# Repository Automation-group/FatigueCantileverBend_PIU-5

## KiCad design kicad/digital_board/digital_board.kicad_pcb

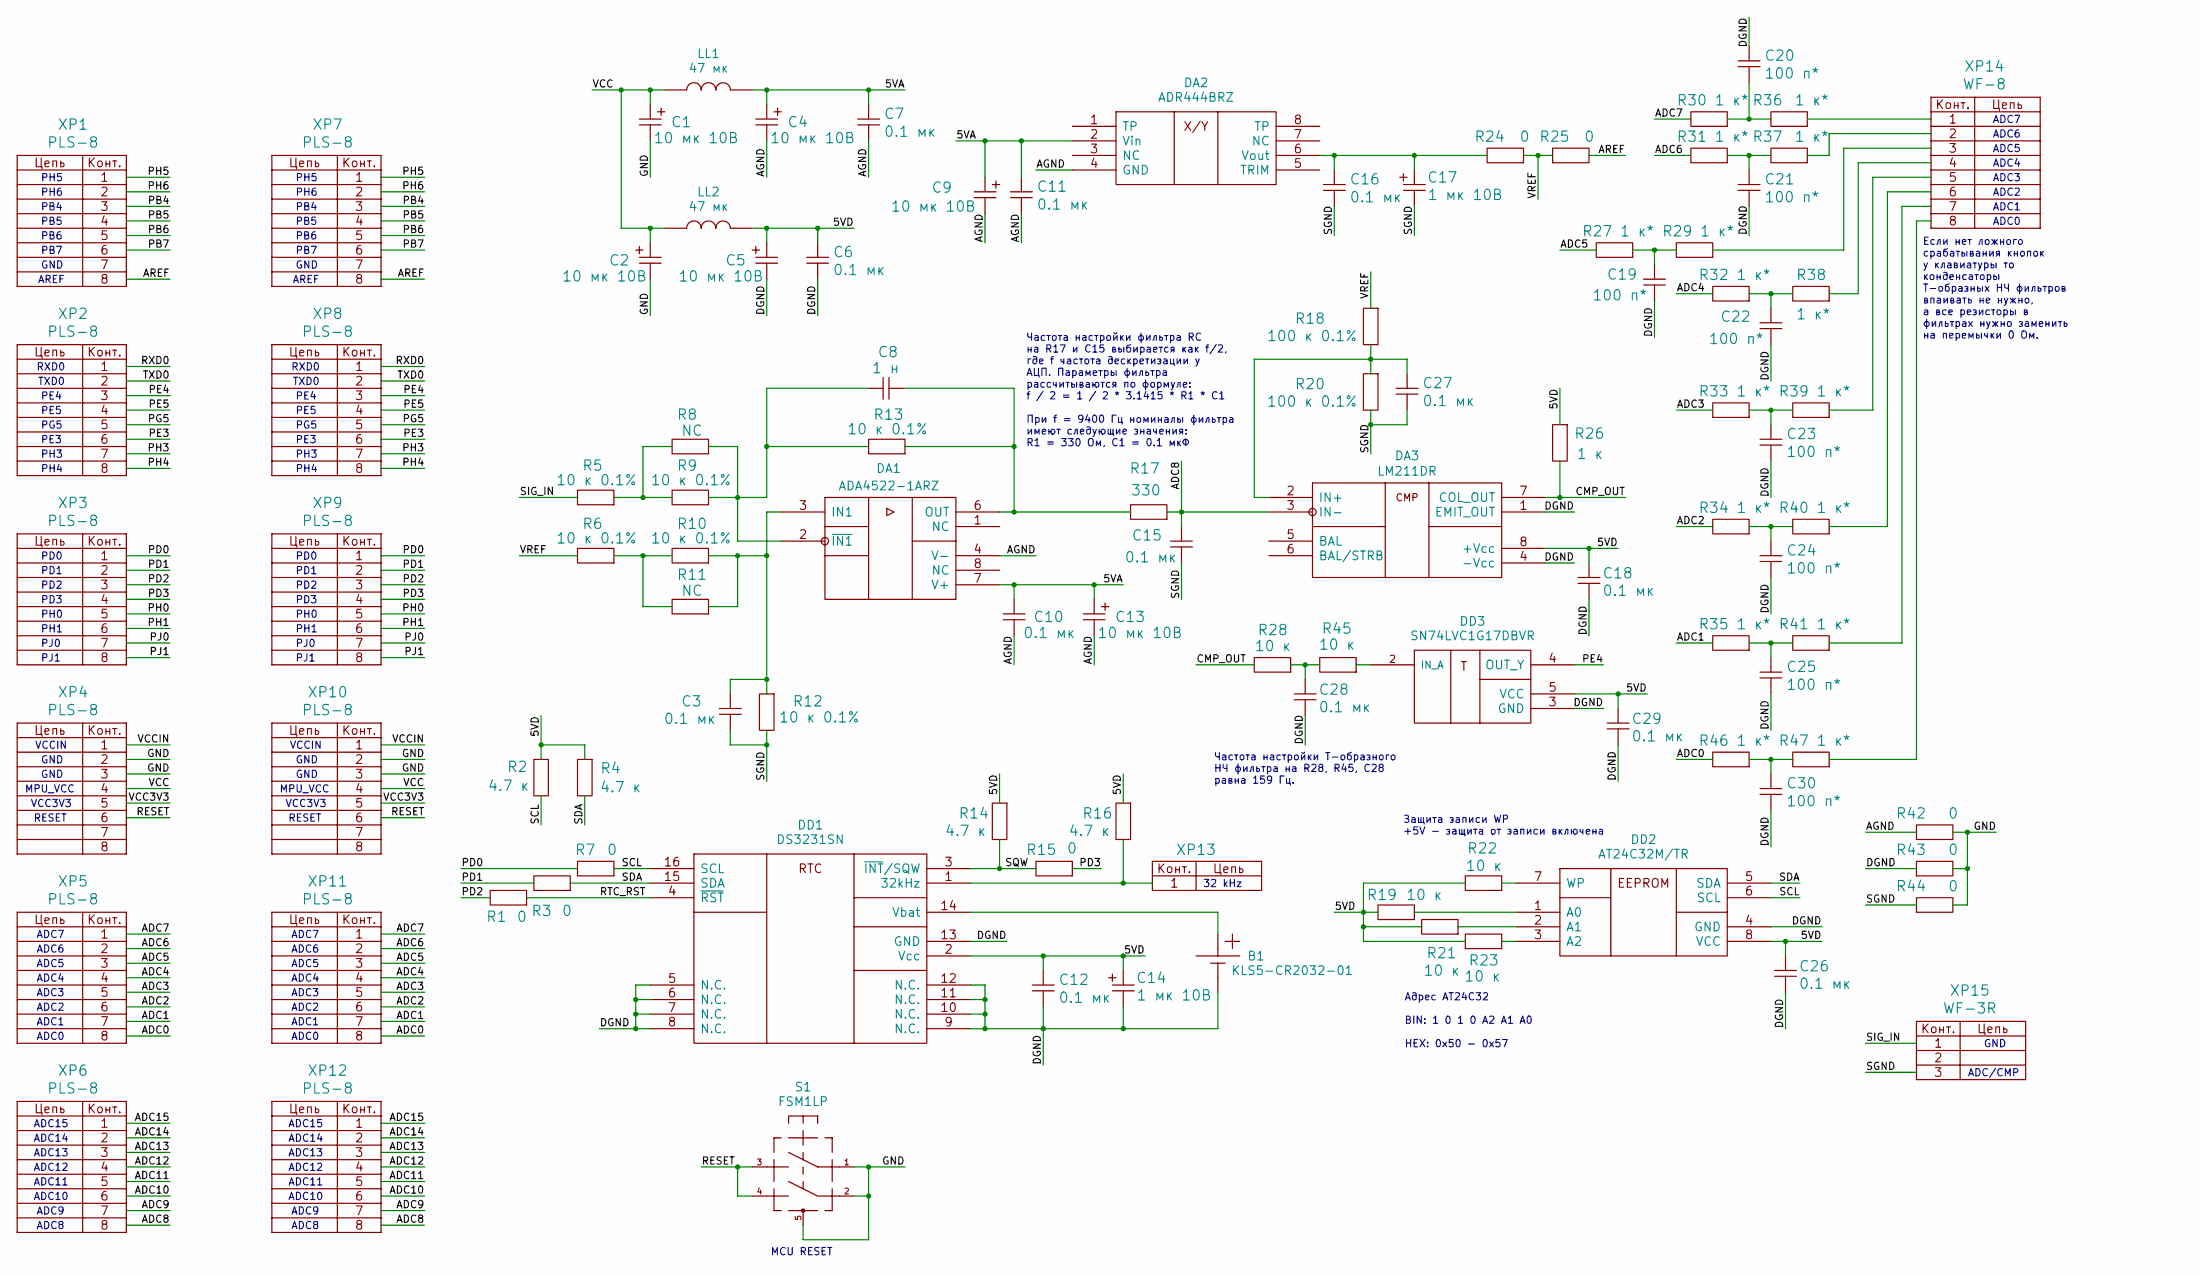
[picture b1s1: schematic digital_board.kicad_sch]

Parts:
B1: KLS5-CR2032-01
C1, C2, C4, C5, C9, C13: 10 мк 10В; CASE_A
C3, C6, C7, C10, C11, C12, C15, C16, C18, C26, C27, C28, C29: 0.1 мк; SMD0805
C8: 1 н; SMD0805
C14, C17: 1 мк 10В; CASE_A
C19, C20, C21, C22, C23, C24, C25, C30: 100 п*; SMD0805
DA1: ADA4522-1ARZ; SOIC8
DA2: ADR444BRZ; SOIC8
DA3: LM211DR; SOIC8
DD1: DS3231SN; SOIC16_RW16
DD2: AT24C32M/TR; SOIC8
DD3: SN74LVC1G17DBVR; SOT753
LL1, LL2: 47 мк; SMD0805
R1, R3, R7, R15, R24, R25, R42, R43, R44: 0; SMD0805
R2, R4, R14, R16: 4.7 к; SMD0805
R5, R6, R9, R10, R12, R13: 10 к 0.1%; SMD0805
R8, R11: NC; SMD0805
R17: 330; SMD0805
R18, R20: 100 к 0.1%; SMD0805
R19, R21, R22, R23, R28, R45: 10 к; SMD0805
R26: 1 к; SMD0805
R27, R29, R30, R31, R32, R33, R34, R35, R36, R37, R38, R39, R40, R41, R46, R47: 1 к*; SMD0805
S1: FSM1LP; SWD_BUTTON
XP1, XP2, XP3, XP4, XP5, XP6, XP7, XP8, XP9, XP10, XP11, XP12: PLS-8; PIN_ARRAY_8x1
XP13: 1_pin_1_0mm
XP14: WF-8
XP15: WF-3R

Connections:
/5VA: C4.1, C7.1, C9.1, C10.1, C11.1, C13.1, DA1.7 (V+), DA2.2 (Vin), LL1.1
/5VD: C5.1, C6.1, C12.1, C14.1, C18.1, C26.1, C29.1, DA3.8 (+Vcc), DD1.2 (Vcc), DD2.8 (VCC), DD3.5 (VCC), LL2.2, R2.1, R4.1, R14.1, R16.1, R19.2, R21.2, R22.2, R23.2, R26.1
/ADC0: R46.2, XP5.8, XP11.8
/ADC1: R35.2, XP5.7, XP11.7
/ADC2: R34.2, XP5.6, XP11.6
/ADC3: R33.2, XP5.5, XP11.5
/ADC4: R32.2, XP5.4, XP11.4
/ADC5: R27.2, XP5.3, XP11.3
/ADC6: R31.2, XP5.2, XP11.2
/ADC7: R30.2, XP5.1, XP11.1
/ADC8: C15.1, DA3.3 (IN-), R17.1, XP6.8, XP12.8
/ADC9: XP6.7, XP12.7
/ADC10: XP6.6, XP12.6
/ADC11: XP6.5, XP12.5
/ADC12: XP6.4, XP12.4
/ADC13: XP6.3, XP12.3
/ADC14: XP6.2, XP12.2
/ADC15: XP6.1, XP12.1
/AGND: C4.2, C7.2, C9.2, C10.2, C11.2, C13.2, DA1.4 (V-), DA2.4 (GND), R42.1
/AREF: R25.2, XP1.8, XP7.8
/CMP_OUT: DA3.7 (COL_OUT), R26.2, R28.2
/DGND: B1.2, C5.2, C6.2, C12.2, C14.2, C18.2, C19.2, C20.1, C21.2, C22.2, C23.2, C24.2, C25.2, C26.2, C28.2, C29.2, C30.2, DA3.1 (EMIT_OUT), DA3.4 (-Vcc), DD1.5 (N.C.), DD1.6 (N.C.), DD1.7 (N.C.), DD1.8 (N.C.), DD1.9 (N.C.), DD1.10 (N.C.), DD1.11 (N.C.), DD1.12 (N.C.), DD1.13 (GND), DD2.4 (GND), DD3.3 (GND), R43.1
/GND: C1.2, C2.2, R42.2, R43.2, R44.2, S1.1, S1.2, S1.5, XP4.2, XP4.3, XP10.2, XP10.3
/PB4: XP1.3, XP7.3
/PB5: XP1.4, XP7.4
/PB6: XP1.5, XP7.5
/PB7: XP1.6, XP7.6
/PD0: R7.2, XP3.1, XP9.1
/PD1: R3.2, XP3.2, XP9.2
/PD2: R1.2, XP3.3, XP9.3
/PD3: R15.1, XP3.4, XP9.4
/PE3: XP2.6, XP8.6
/PE4: DD3.4 (OUT_Y), XP2.3, XP8.3
/PE5: XP2.4, XP8.4
/PG5: XP2.5, XP8.5
/PH0: XP3.5, XP9.5
/PH1: XP3.6, XP9.6
/PH3: XP2.7, XP8.7
/PH4: XP2.8, XP8.8
/PH5: XP1.1, XP7.1
/PH6: XP1.2, XP7.2
/PJ0: XP3.7, XP9.7
/PJ1: XP3.8, XP9.8
/RESET: S1.3, S1.4, XP4.6, XP10.6
/RTC_RST: DD1.4 (~RST), R1.1
/RXD0: XP2.1, XP8.1
/SCL: DD1.16 (SCL), DD2.6 (SCL), R2.2, R7.1
/SDA: DD1.15 (SDA), DD2.5 (SDA), R3.1, R4.2
/SGND: C3.2, C15.2, C16.2, C17.2, C27.2, R12.2, R20.2, R44.1, XP15.3
/SIG_IN: R5.2, XP15.1
/SQW: DD1.3 (~INT/SQW), R14.2, R15.2
/TXD0: XP2.2, XP8.2
/VCC: C1.1, C2.1, LL1.2, LL2.1, XP4.4, XP10.4
/VCC3V3: XP4.5, XP10.5
/VCCIN: XP4.1, XP10.1
/VREF: R6.2, R18.1, R24.1, R25.1
unnamed: C19.1, R27.1, R29.2
unnamed: C20.2, R30.1, R36.2
unnamed: C21.1, R31.1, R37.2
unnamed: C22.1, R32.1, R38.2
unnamed: C23.1, R33.1, R39.2
unnamed: C24.1, R34.1, R40.2
unnamed: C25.1, R35.1, R41.2
unnamed: C28.1, R28.1, R45.2
unnamed: C30.1, R46.1, R47.2
unnamed: C3.1, DA1.3 (IN1), R10.1, R11.1, R12.1
unnamed: C8.2, DA1.6 (OUT), R13.1, R17.2
unnamed: C8.1, DA1.2 (~IN1), R8.1, R9.1, R13.2
unnamed: C16.1, C17.1, DA2.6 (Vout), R24.2
unnamed: C27.1, DA3.2 (IN+), R18.2, R20.1
unnamed: DD1.1 (32kHz), R16.2, XP13.1
unnamed: B1.1, DD1.14 (Vbat)
unnamed: DD2.1 (A0), R19.1
unnamed: DD2.2 (A1), R21.1
unnamed: DD2.3 (A2), R23.1
unnamed: DD2.7 (WP), R22.1
unnamed: DD3.2 (IN_A), R45.1
unnamed: R5.1, R8.2, R9.2
unnamed: R6.1, R10.2, R11.2
unnamed: R29.1, XP14.3
unnamed: R36.1, XP14.1
unnamed: R37.1, XP14.2
unnamed: R38.1, XP14.4
unnamed: R39.1, XP14.5
unnamed: R40.1, XP14.6
unnamed: R41.1, XP14.7
unnamed: R47.1, XP14.8

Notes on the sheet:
ADC4
ADC3
RXD0
ADC11
Если нет ложного срабатывания кнопок у клавиатуры то конденсаторы Т-образных НЧ фильтров впаивать не нужно, а все резисторы в фильтрах нужно заменить на перемычки 0 Ом.
VCCIN
TXD0
ADC5
PE3
MPU_VCC
ADC7
ADC14
PB7
PH0
GND
ADC8
ADC/CMP
PD1
PE4
PG5
ADC0
ADC6
ADC9
PD3
PB5
ADC15
ADC13
ADC10
PH5
PB6
PH4
PH6
PD2
PB4
PH3
ADC12
Адрес AT24C32 BIN: 1 0 1 0 A2 A1 A0 HEX: 0x50 - 0x57
PJ1
Частота настройки Т-образного НЧ фильтра на R28, R45, С28 равна 159 Гц.
32 kHz

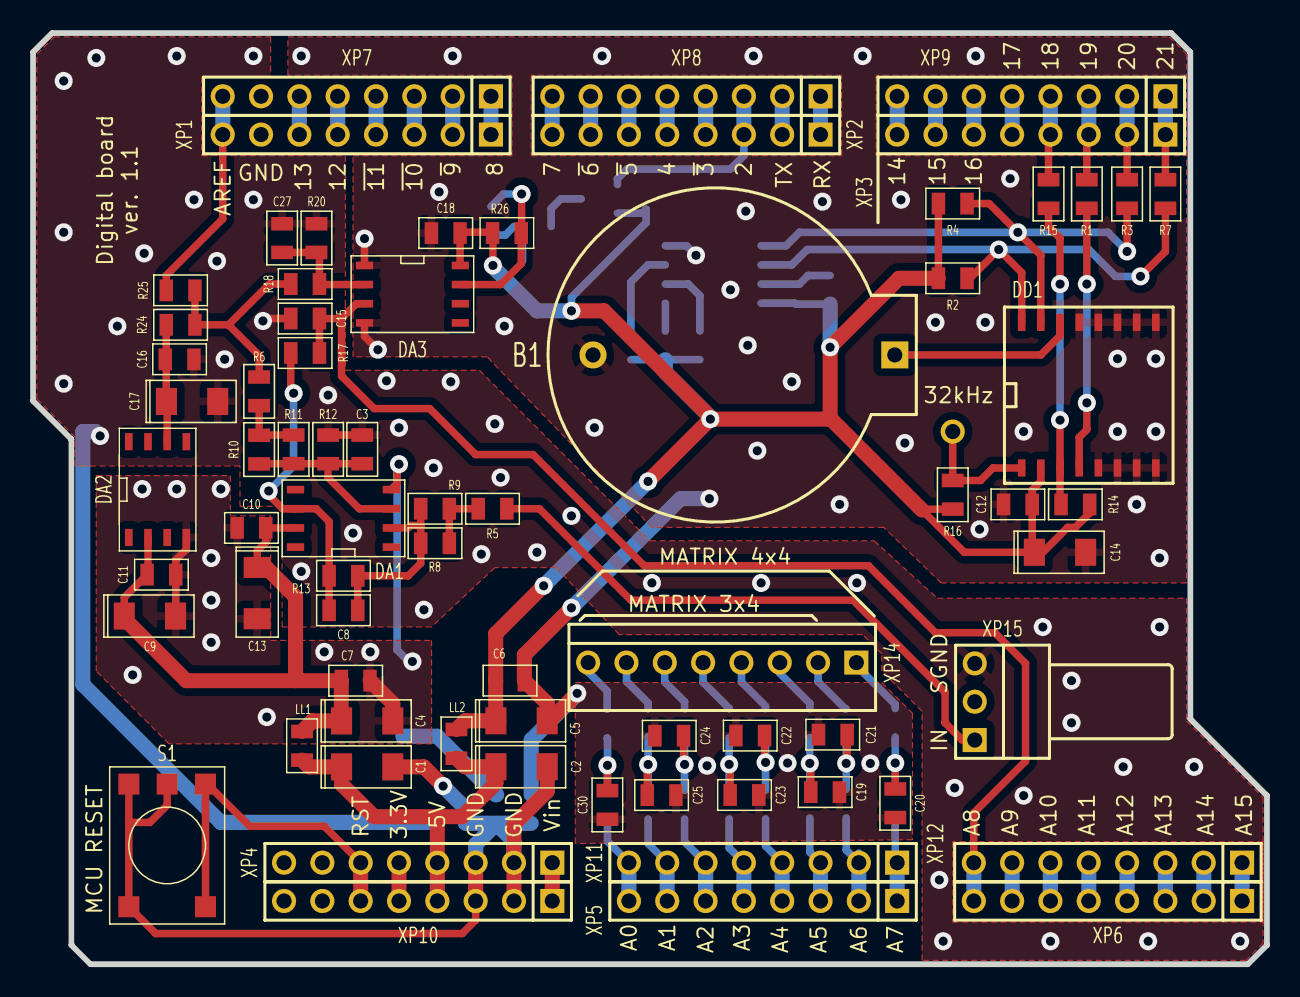
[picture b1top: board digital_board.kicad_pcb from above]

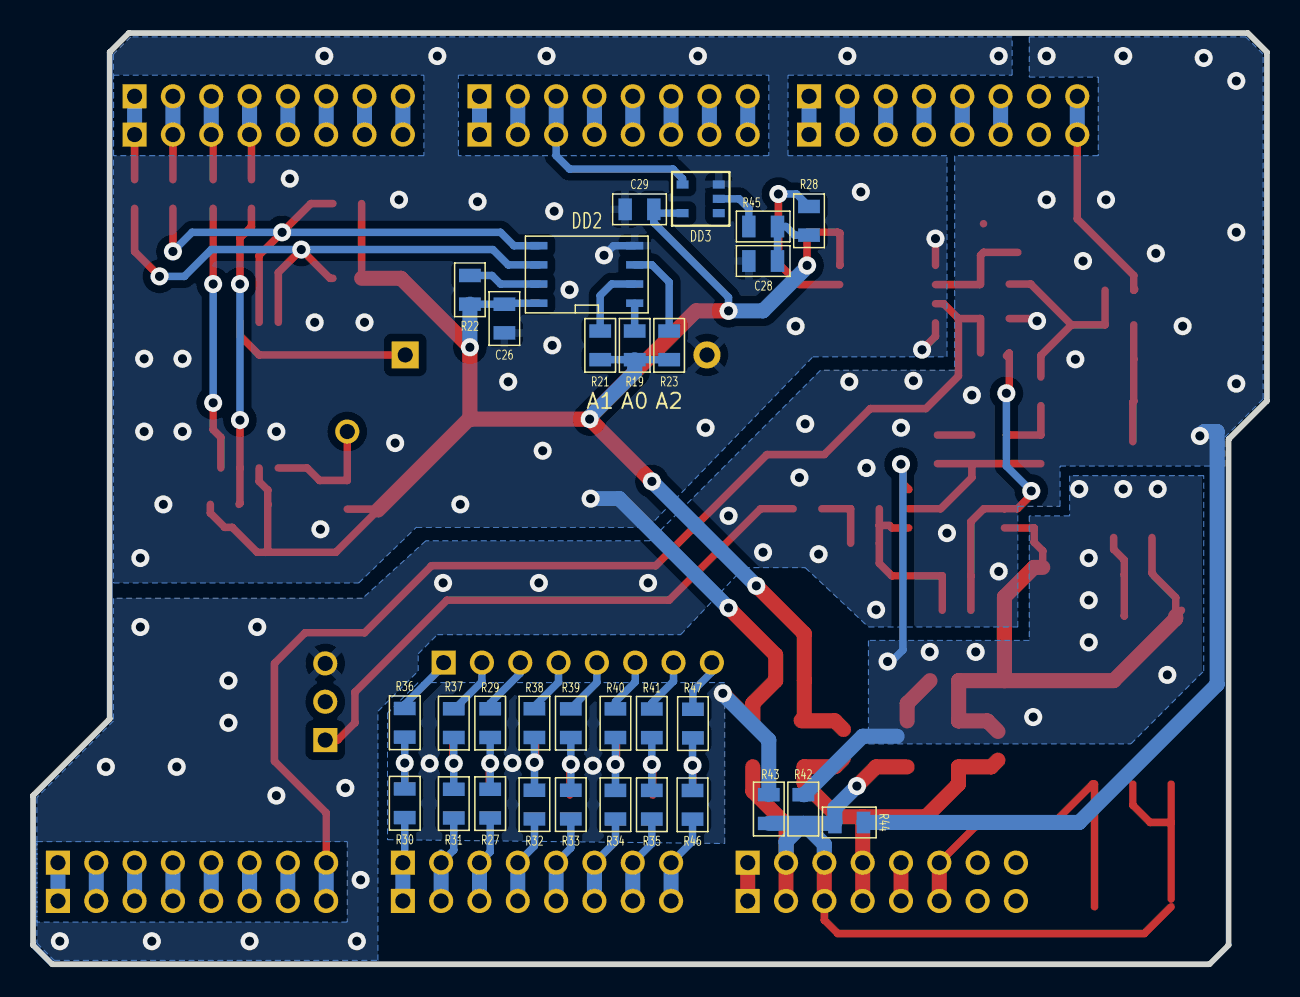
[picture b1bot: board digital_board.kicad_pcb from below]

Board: 2 copper layers, 81.8 x 61.7 mm, 102 parts (30 on the bottom side), 87 nets.

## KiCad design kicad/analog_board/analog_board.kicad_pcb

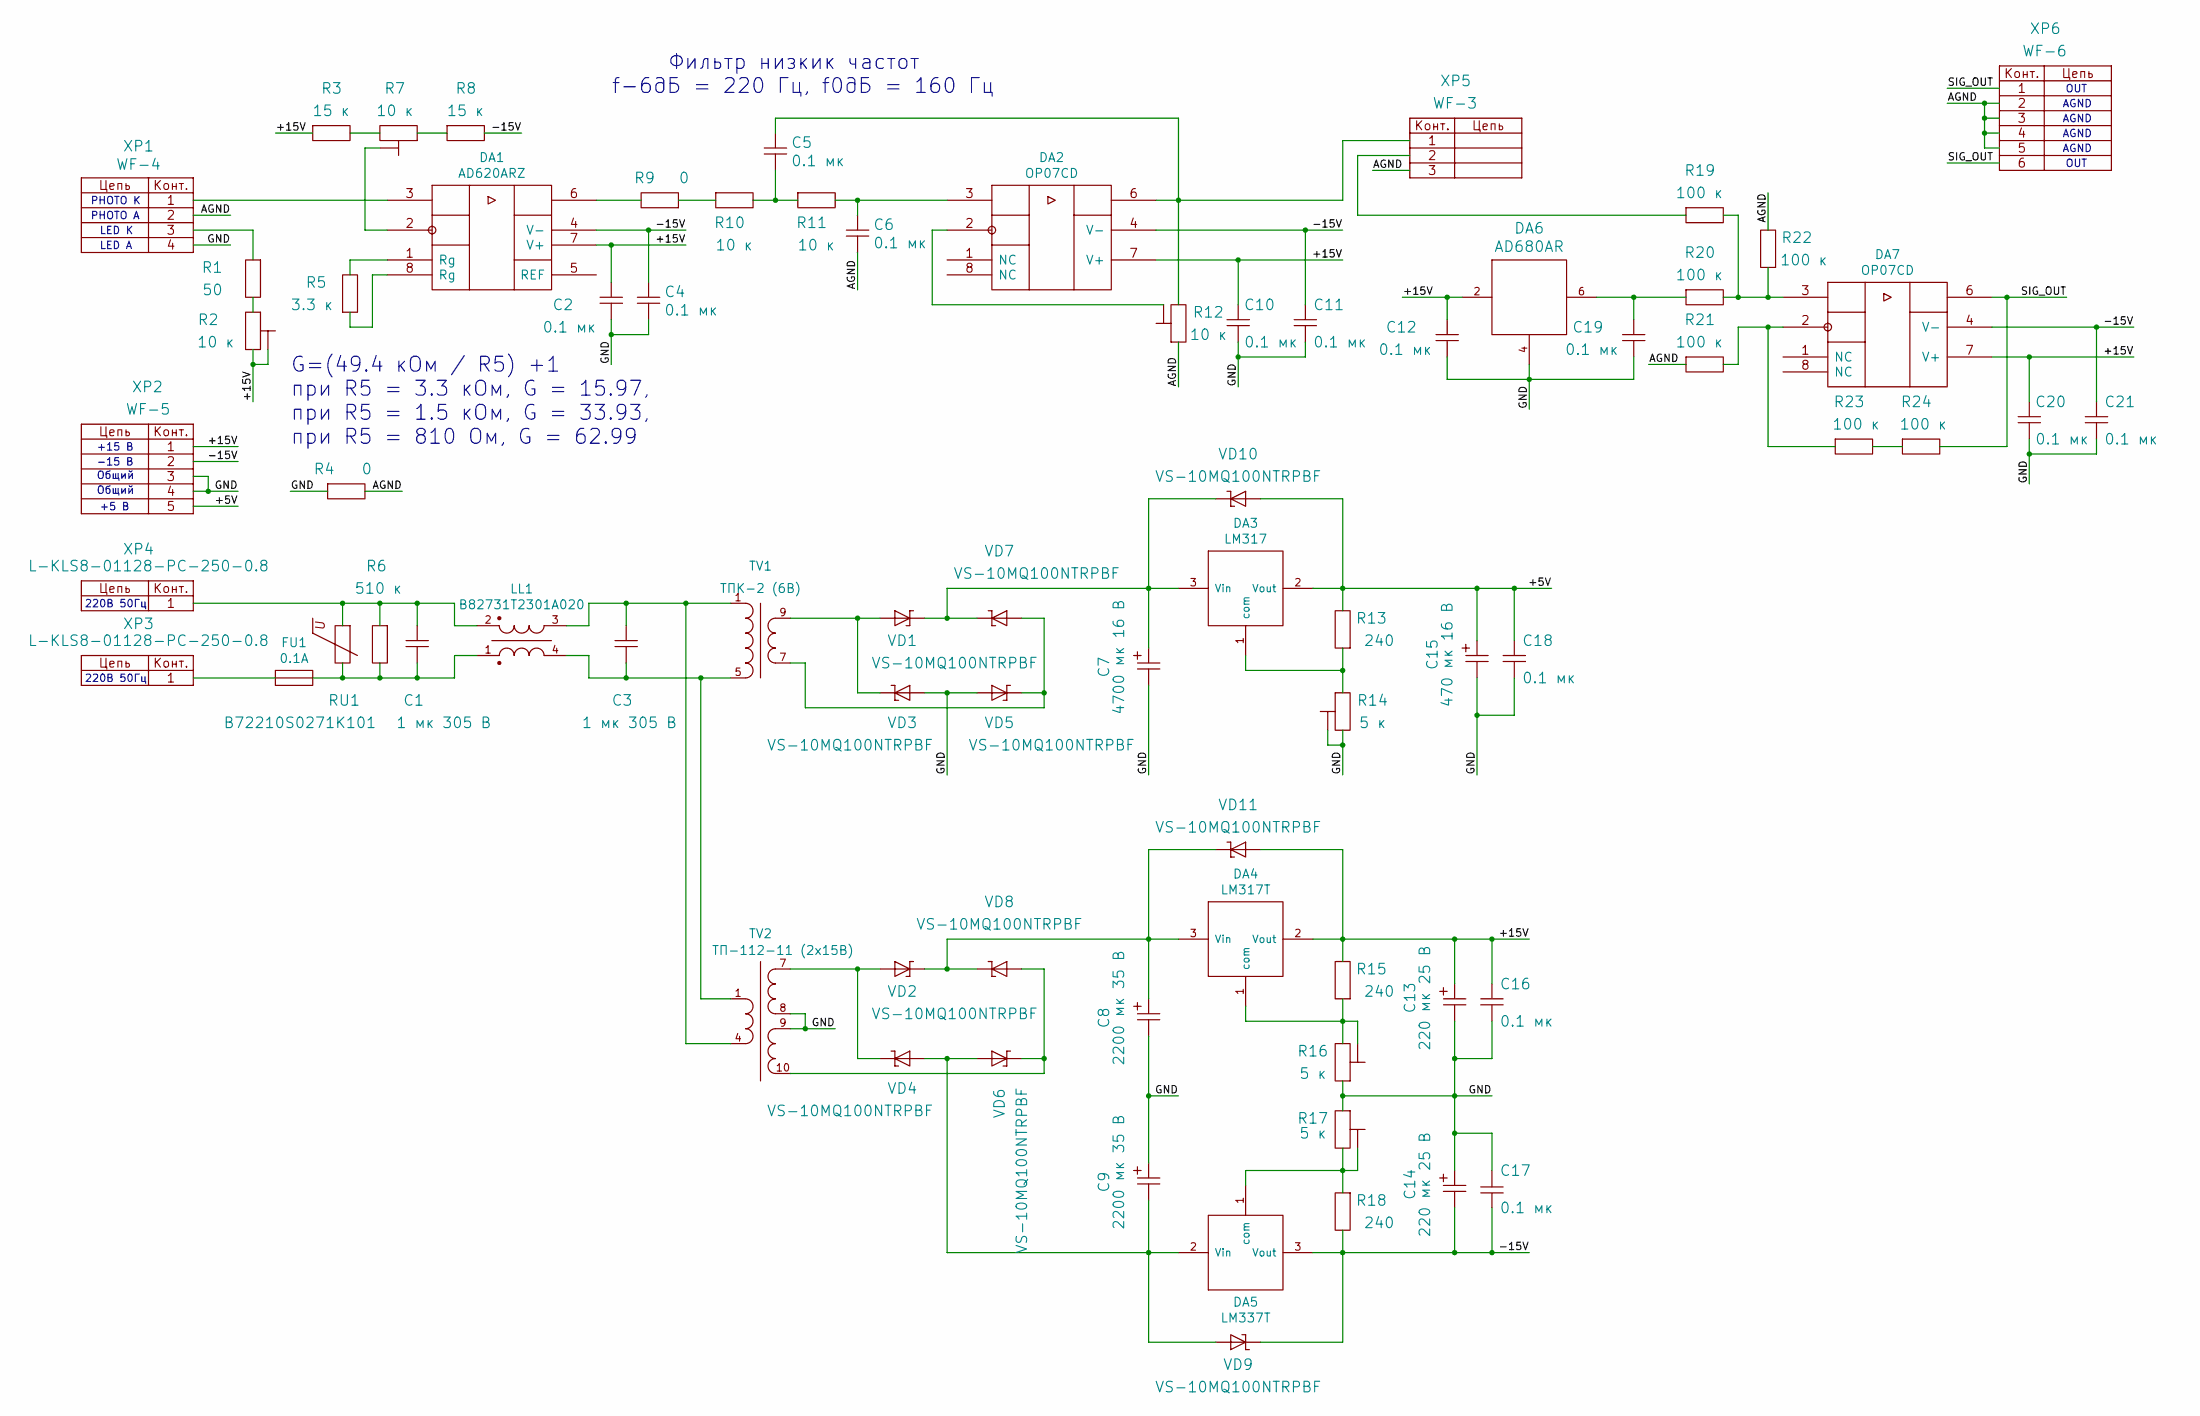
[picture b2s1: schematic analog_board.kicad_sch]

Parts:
C1, C3: 1 мк 305 В; CAPACITOR_B32923_26.5x11
C2, C4, C5, C6, C10, C11, C12, C16, C17, C18, C19, C20, C21: 0.1 мк; SMD0805
C7: 4700 мк 16 В; CAPACITOR_7.62_D16
C8, C9: 2200 мк 35 В; CAPACITOR_7.62_D16
C13, C14: 220 мк 25 В; CAPACITOR_3_D8
C15: 470 мк 16 В; CAPACITOR_3_D8
DA1: AD620ARZ; SOIC8
DA2, DA7: OP07CD; SOIC8
DA3: LM317; TO220_RAD_16.5x15
DA4: LM317T; TO220_RAD_16.5x15
DA5: LM337T; TO220_RAD_16.5x15
DA6: AD680AR; SOIC8
FU1: 0.1A; FU_PTF15B
LL1: B82731T2301A020; EMI_EPCOS_B82731T
R1: 50; SMD0805
R2, R7, R12: 10 к; Electron_3296W
R3, R8: 15 к; SMD0805
R4, R9: 0; SMD0805
R5: 3.3 к; SMD0805
R6: 510 к; SMD2512
R10, R11: 10 к; SMD0805
R13, R15, R18: 240; SMD0805
R14, R16, R17: 5 к; Electron_3296W
R19, R20, R21, R22, R23, R24: 100 к; SMD0805
RU1: B72210S0271K101; RU_EPCOS_B72210S0271K101_12х5
TV1: ТПК-2 (6В); TPG2-12
TV2: ТП-112-11 (2х15В); TP112-11
VD1, VD2, VD3, VD4, VD5, VD6, VD7, VD8, VD9, VD10, VD11: VS-10MQ100NTRPBF; SMA
XP1: WF-4
XP2: WF-5
XP3, XP4: L-KLS8-01128-PC-250-0.8; TERMINAL_KLS8-01128_6.3mm
XP5: WF-3
XP6: WF-6

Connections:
/+5V: C15.1, C18.1, DA3.2 (Vout), R13.2, VD10.1, XP2.5
/+15V: C2.1, C10.1, C12.1, C13.1, C16.1, C20.1, DA1.7 (V+), DA2.7 (V+), DA4.2 (Vout), DA6.2 (Vin), DA7.7 (V+), R2.2, R2.3, R3.1, R15.2, VD11.1, XP2.1
/-15V: C4.1, C11.1, C14.2, C17.1, C21.1, DA1.4 (V-), DA2.4 (V-), DA5.3 (Vout), DA7.4 (V-), R8.2, R18.2, VD9.2, XP2.2
/AGND: C6.2, R4.2, R12.1, R21.1, R22.2, XP1.2, XP5.3, XP6.2, XP6.3, XP6.4, XP6.5
/GND: C2.2, C4.2, C7.2, C8.2, C9.1, C10.2, C11.2, C12.2, C13.2, C14.1, C15.2, C16.2, C17.2, C18.2, C19.2, C20.2, C21.2, DA6.4 (Gnd), R4.1, R14.2, R14.3, R16.1, R17.1, TV2.8, TV2.9, VD3.1, VD5.1, XP1.4, XP2.3, XP2.4
/SIG_OUT: DA7.6, R24.2, XP6.1, XP6.6
unnamed: C1.1, LL1.2, R6.1, RU1.1, XP4.1
unnamed: C1.2, FU1.2, LL1.1, R6.2, RU1.2
unnamed: C3.1, LL1.3, TV1.1, TV2.4
unnamed: C3.2, LL1.4, TV1.5, TV2.1
unnamed: C5.1, DA2.6, R12.3, XP5.1
unnamed: C5.2, R10.2, R11.1
unnamed: C6.1, DA2.3, R11.2
unnamed: C7.1, DA3.3 (Vin), VD1.2, VD7.2, VD10.2
unnamed: C8.1, DA4.3 (Vin), VD2.2, VD8.2, VD11.2
unnamed: C9.2, DA5.2 (Vin), VD4.1, VD6.1, VD9.1
unnamed: C19.1, DA6.6 (Vout), R20.1
unnamed: DA1.1 (Rg), R5.2
unnamed: DA1.2, R7.2
unnamed: DA1.3, XP1.1
unnamed: DA1.6, R9.2
unnamed: DA1.8 (Rg), R5.1
unnamed: DA2.2, R12.2
unnamed: DA3.1 (com), R13.1, R14.1
unnamed: DA4.1 (com), R15.1, R16.2, R16.3
unnamed: DA5.1 (com), R17.2, R17.3, R18.1
unnamed: DA7.2, R21.2, R23.1
unnamed: DA7.3, R19.2, R20.2, R22.1
unnamed: FU1.1, XP3.1
unnamed: R1.1, XP1.3
unnamed: R1.2, R2.1
unnamed: R3.2, R7.3
unnamed: R7.1, R8.1
unnamed: R9.1, R10.1
unnamed: R19.1, XP5.2
unnamed: R23.2, R24.1
unnamed: TV1.7, VD5.2, VD7.1
unnamed: TV1.9, VD1.1, VD3.2
unnamed: TV2.7, VD2.1, VD4.2
unnamed: TV2.10, VD6.2, VD8.1

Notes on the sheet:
-15 В
Фильтр низкик частот f-6дБ = 220 Гц, f0дБ = 160 Гц
Общий
PHOTO A
AGND
LED A
OUT
G=(49.4 кОм / R5) +1 при R5 = 3.3 кОм, G = 15.97, при R5 = 1.5 кОм, G = 33.93, при R5 = 810 Ом, G = 62.99
LED K
220В 50Гц
+5 В
+15 В
PHOTO K

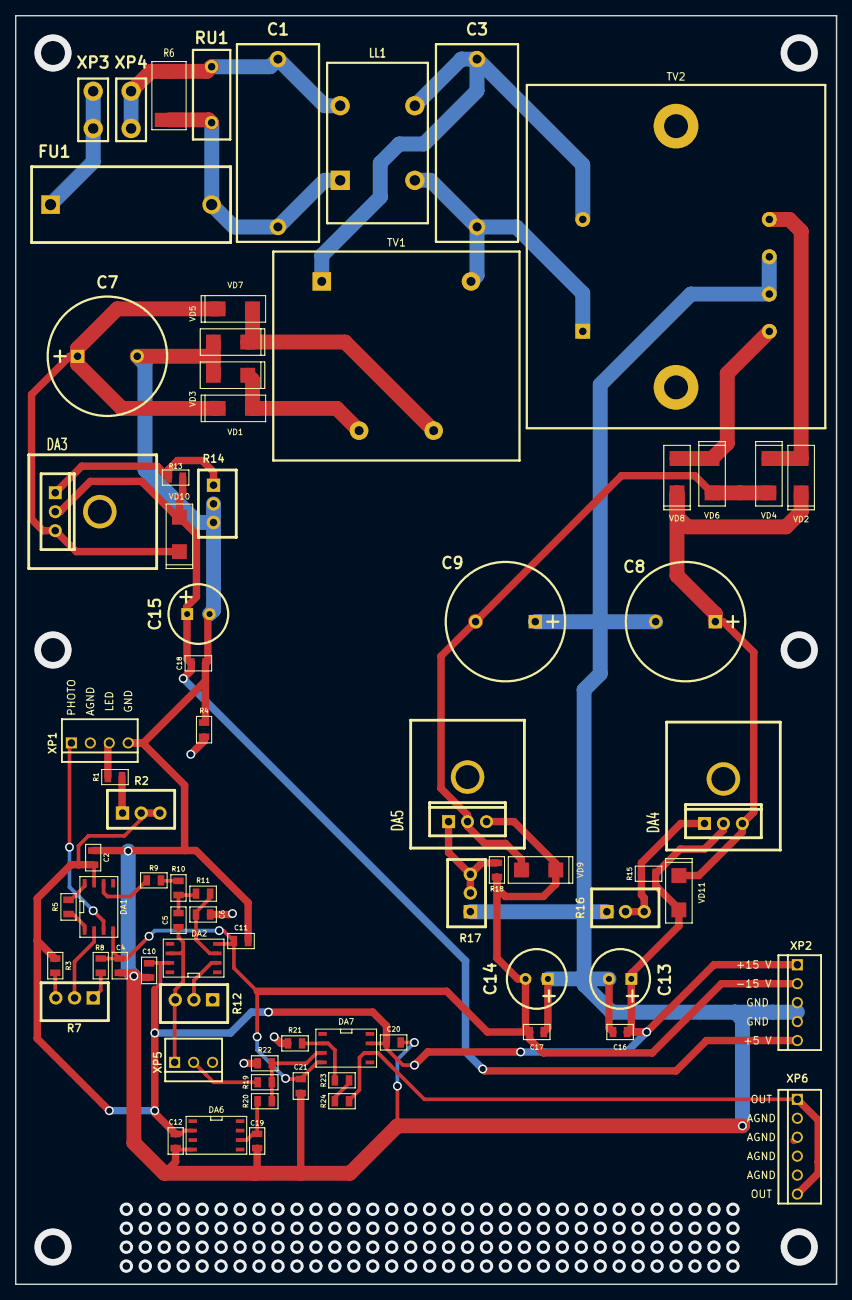
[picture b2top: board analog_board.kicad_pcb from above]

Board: 2 copper layers, 110.0 x 170.0 mm, 74 parts (0 on the bottom side), 40 nets.

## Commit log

2025-06-06 First commit.
2025-06-10 Приступил к трассировке печатной платы.
2025-06-11 Закончил трассировку цифровой печатной платы.
2025-06-19 Отправил печатные платы digital_board в производство.
2025-10-17 Закончил проверку работоспособности цифровой платы.
2025-10-20 Исправил ошибки в схеме и на печатной плате. Увеличил версию цифровой платы до 1.1.
2025-11-01 Добавил программу для расчёта прогиба образца с радиусом.
2025-11-01 Добавил исключение для файлов ресурсов rc.
2025-11-05 Поправил программу после сборки в Windows.
2025-11-11 Дбавил возможность сборки для Qt5/Qt6 и автоматический поиск dll библиотек в Windows (MinGW).
2025-11-14 Добавил новые опции для расчёта и присвоил программе версию 0.2
2025-11-18 Добавил возможность задания размера и формы шрифта в программе.
2025-11-18 Поправил название переменных в расчёте и приступил к созданию окна с информацией о программе.
2025-11-19 Добавил иконки в формате svg.
2025-11-21 Добавил чертежи подвижной системы в формате svg.
2025-11-24 Добавил конвертор svg в QPixmap.
2025-11-25 Добавил информацию о программе и её разработчиках в отдельном окошке.
2025-11-26 Закончил разработку интерфейса программы.
2025-11-28 Приступил к написанию документации для программы.
2025-12-04 Продолжил описание алгоритма расчёта.
2025-12-05 Продолжил написание документации к программе.
2025-12-09 Продолжил написание документации.
2025-12-12 Продолжил писать документацию к программе, исправил грубую ошибку при расчёте sigma_max при приложении силы по оси x.
2025-12-19 Закончил написание алгоритма расчёта прогиба.
2025-12-25 Сделал мелкие правки в документации для программы CalcDeflection.
2025-12-26 Исправил все предупреждения при компиляции документации в latex.
2026-04-01 Приступил к переосмыслению схемы аналоговой платы.
2026-05-08 Добавил новую схему усилителя для фотодиода.
